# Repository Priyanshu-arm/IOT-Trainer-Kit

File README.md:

An educational development board designed for hands-on learning of IoT fundamentals using the ESP32. Ideal for students, educators, and enthusiasts to prototype sensor-based applications.

Key Components:

LDR (Light Dependent Resistor) – for light sensing

Relay Module – for high-voltage switching

LEDs – for visual output

Buzzer

Push Buttons & DIP Switches

TFT Display

RGB LED

Features:

Modular layout for easy understanding

Compatible with Arduino/ESP32 frameworks

Ready for classroom/lab demonstrations

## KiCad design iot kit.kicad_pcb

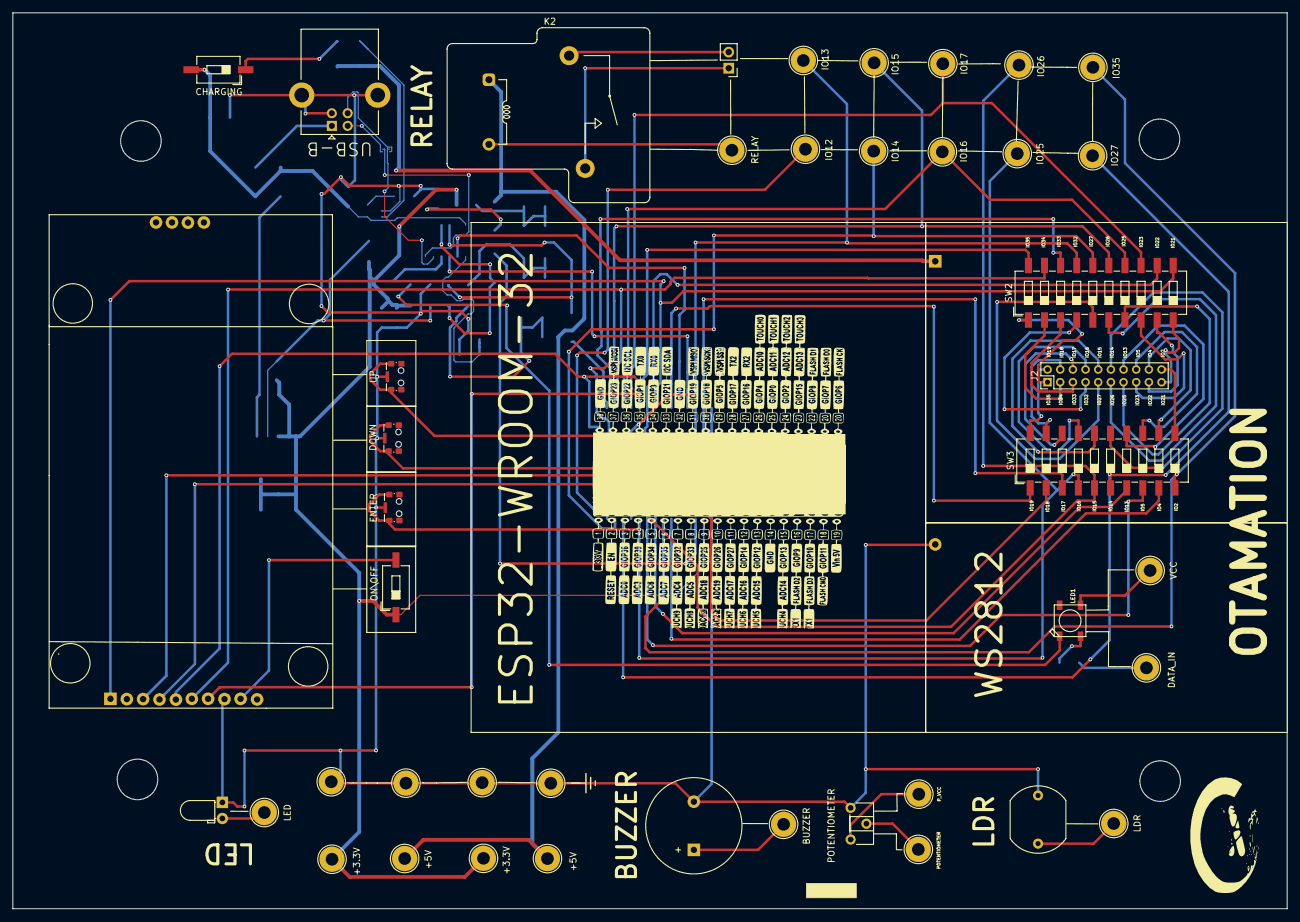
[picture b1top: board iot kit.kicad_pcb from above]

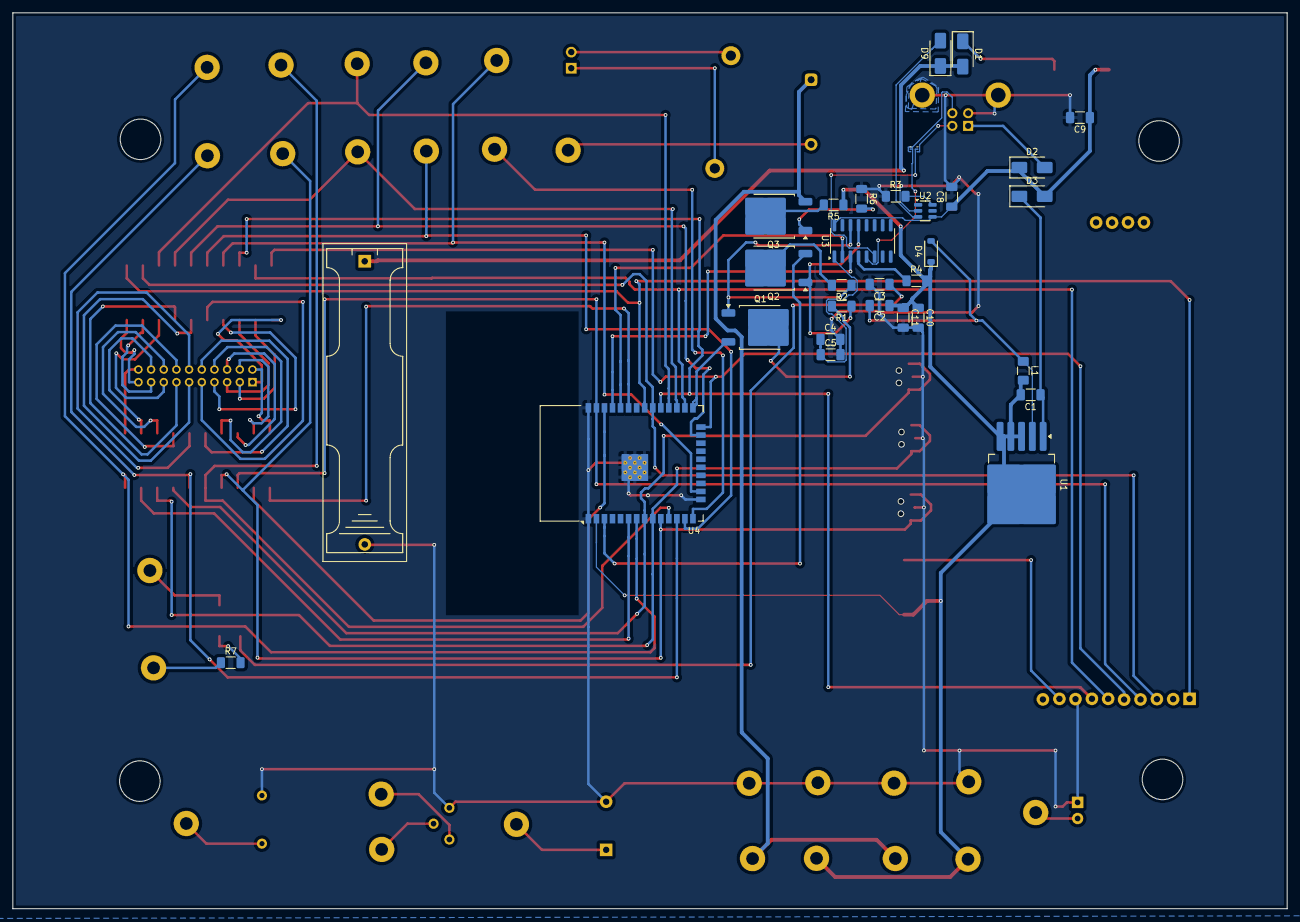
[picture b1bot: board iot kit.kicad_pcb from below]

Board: 2 copper layers, 201.2 x 141.4 mm, 80 parts (32 on the bottom side), 65 nets.

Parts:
BT1: Battery_Cell; BatteryHolder_Keystone_2466_1xAAA
BZ1: Buzzer; Buzzer_15x7.5RM7.6
C1: 100uF; C_1206_3216Metric_Pad1.33x1.80mm_HandSolder
C2: 1000uF; C_1206_3216Metric_Pad1.33x1.80mm_HandSolder
C3: 100nF; C_1206_3216Metric_Pad1.33x1.80mm_HandSolder
C4, C9, C11: 10uf; C_1206_3216Metric_Pad1.33x1.80mm_HandSolder
C5, C8, C10: 0.1uf; C_1206_3216Metric_Pad1.33x1.80mm_HandSolder
CHARGING: SW_DIP_x01; SW_DIP_SPSTx01_Slide_6.7x4.1mm_W8.61mm_P2.54mm_LowProfile
D1, D2, D3, D9: SS14; D_SMA
D4: MBR0560; D_SOD-123
D5: LED; LED_D3.0mm_Horizontal_O1.27mm_Z2.0mm
D7, D8: D_TVS; Nexperia_DSN0603-2_0.6x0.3mm_P0.4mm
DATA_IN: TestPoint; TestPoint_THTPad_D4.0mm_Drill2.0mm
DOWN: CK_KMS2xxG; SW_SPST_CK_KMS2xxGP
ENTER: CK_KMS2xxG; SW_SPST_CK_KMS2xxGP
G7, G11: LOGO; 456rect
G*7411: LOGO; 456rect
GMAIN: LOGO; esppppppppp
IO12, IO13, IO14, IO15, IO16, IO17, IO25, IO26, IO27, IO35: TestPoint; TestPoint_THTPad_D4.0mm_Drill2.0mm
J1: USB_B; USB_B_Lumberg_2411_02_Horizontal
J2: Conn_02x10_Odd_Even; PinHeader_2x10_P2.00mm_Vertical
J6: Screw_Terminal_01x02; PinHeader_1x02_P2.54mm_Vertical
K2: RAYEX-L90AS; Relay_SPST_RAYEX-L90AS
L1: 100uH; L_1206_3216Metric_Pad1.42x1.75mm_HandSolder
L2: SPI TFT DISPLAY; TFT
LDR: TestPoint; TestPoint_THTPad_D4.0mm_Drill2.0mm
LED: TestPoint; TestPoint_THTPad_D4.0mm_Drill2.0mm
LED1: WS2812B
ON\OFF: SW_DIP_x01; SW_DIP_SPSTx01_Slide_6.7x4.1mm_W8.61mm_P2.54mm_LowProfile
POTENTIOMETER: TestPoint; TestPoint_THTPad_D4.0mm_Drill2.0mm
P_VCC: TestPoint; TestPoint_THTPad_D4.0mm_Drill2.0mm
Q1, Q2, Q3: S8050; TO-252-2
R1, R2: 10K; R_1206_3216Metric_Pad1.30x1.75mm_HandSolder
R3, R5, R6: 1K; R_1206_3216Metric_Pad1.30x1.75mm_HandSolder
R4: 0; R_1206_3216Metric_Pad1.30x1.75mm_HandSolder
R7: 330; R_1206_3216Metric_Pad1.30x1.75mm_HandSolder
R10: LDR03; R_LDR_10x8.5mm_P7.6mm_Vertical
RELAY: TestPoint; TestPoint_THTPad_D4.0mm_Drill2.0mm
RV1: R_Potentiometer; Potentiometer_ACP_CA6-H2,5_Horizontal
SW2, SW3: SW_DIP_x10; SW_DIP_SPSTx10_Slide_6.7x26.96mm_W8.61mm_P2.54mm_LowProfile
TP1, TP2, TP3, TP4, TP7, TP20, TP21, TP25, TP26: TestPoint; TestPoint_THTPad_D4.0mm_Drill2.0mm
U1: LM2576HVS-3.3; TO-263-5_TabPin3
U2: TP4057; TSOT-23-6
U3: CH340C; SOIC-16_3.9x9.9mm_P1.27mm
U4: ESP32-WROOM-32
UP: CK_KMS2xxG; SW_SPST_CK_KMS2xxGP
VCC: TestPoint; TestPoint_THTPad_D4.0mm_Drill2.0mm
g22: LOGO; 456rect

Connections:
+3.3V: C1.2, C2.1, C10.1, C11.1, D4.1 (K), L1.2, ON\OFF.1, R4.2, R5.1, U1.3 (GND), U1.4 (FB), U1.5 (~ON/OFF), U4.2 (VDD)
/+5V_BUS: C8.1, C9.1, CHARGING.2, D2.1 (K), D3.2 (A), U2.4 (V_{CC}), U3.16 (VCC)
/+VE_B: D1.2 (A), D9.1 (K)
/D+: D7.1 (A1), U3.5 (UD+)
/D-: D8.1 (A1), U3.6 (UD-)
/IO2: SW2.20, U4.24 (IO2)
/IO4: SW2.19, U4.26 (IO4)
/IO5: SW2.18, U4.29 (IO5)
/IO13: SW2.17, U4.16 (IO13)
/IO14: SW2.16, U4.13 (IO14)
/IO15: SW2.15, U4.23 (IO15)
/IO16: SW2.14, U4.27 (IO16)
/IO17: SW2.13, U4.28 (IO17)
/IO18: SW2.12, U4.30 (IO18)
/IO19: SW2.11, U4.31 (IO19)
/IO21: SW3.1, U4.33 (IO21)
/IO22: SW3.2, U4.36 (IO22)
/IO23: SW3.3, U4.37 (IO23)
/IO25: ENTER.1, SW3.4, U4.10 (IO25)
/IO26: SW3.5, U4.11 (IO26)
/IO27: SW3.6, U4.12 (IO27)
/IO32: SW3.7, U4.8 (IO32), UP.1
/IO33: DOWN.1, SW3.8, U4.9 (IO33)
/IO34: SW3.9, U4.6 (IO34)
/IO35: SW3.10, U4.7 (IO35)
GND: C3.2, C4.2, C5.2, C8.2, C9.2, C10.2, C11.2, DOWN.SH (B), ENTER.SH (B), R3.1, R6.1, U2.2 (GND), U4.1 (GND), U4.15 (GND), U4.38 (GND), U4.39 (GND), UP.SH (B)
GPIO 0: Q1.3 (C), U4.25 (IO0)
unnamed: CHARGING.1, D1.1 (K)
unnamed: C1.1, D3.1 (K), U1.1 (VIN)
unnamed: C2.2, D4.2 (A), L1.1, U1.2 (OUT)
unnamed: D9.2 (A), U2.3 (BAT)
unnamed: J2.1, SW2.1
unnamed: J2.2, SW3.20
unnamed: J2.3, SW2.2
unnamed: J2.4, SW3.19
unnamed: J2.5, SW2.3
unnamed: J2.6, SW3.18
unnamed: J2.7, SW2.4
unnamed: J2.8, SW3.17
unnamed: J2.9, SW2.5
unnamed: J2.10, SW3.16
unnamed: J2.11, SW2.6
unnamed: J2.12, SW3.15
unnamed: J2.13, SW2.7
unnamed: J2.14, SW3.14
unnamed: J2.15, SW2.8
unnamed: J2.16, SW3.13
unnamed: J2.17, SW2.9
unnamed: J2.18, SW3.12
unnamed: J2.19, SW2.10
unnamed: J2.20, SW3.11
unnamed: LED1.4-DIN (DI), R7.2
unnamed: C3.1, LED1.3-GND (GND)
unnamed: Q1.2 (B), R1.2
unnamed: Q2.2 (B), R2.2
unnamed: Q3.2 (B), R5.2
unnamed: Q3.1 (E), R6.2
unnamed: R3.2, U2.6 (PROG)
unnamed: C4.1, C5.1, U3.1 (GND)
unnamed: R4.1, U3.4 (V3)
RST: Q2.3 (C), U4.3 (EN)
UART0 RX: U3.2 (TXD), U4.34 (RXD0/IO3)
UART0_DTR: Q2.1 (E), R1.1, U3.13 (~DTR)
UART0_RTS: Q1.1 (E), R2.1, U3.14 (~RTS)
UART0_TX: U3.3 (RXD), U4.35 (TXD0/IO1)
